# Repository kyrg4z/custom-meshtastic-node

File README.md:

# Custom Meshtastic/Reticulum Node
 
> *Long-range messaging when there's no signal.*

#### Designed by [kyrg4z](https://github.com/kyrg4z)

A custom Meshtastic compatible LoRa communication device that is designed for off-grid messaging in areas where cellular/internet aren't available such as hiking trails, mountains, and forests. This device provides interface for phones to be able to send messages through long range radio through a decentralized mesh network.  

> [!NOTE]
> Read about progress status in JOURNAL.md

### Project Overview
 
A handheld LoRa mesh node built around the Heltec HT-CT62 module (ESP32-C3 + Semtech SX1262), with GPS, a small OLED status display, and a single 18650 cell with USB-C charging and full battery protection. The phone connects over Bluetooth and the node relays messages over 915 MHz LoRa to other nodes in the mesh.

## Story Behind It 

On a chill summer day, while biking in the forest, I tried messaging my friend, but the message didn't go through simply because the cellular signal was too weak there. 
That day I decided to build something of my own, so meeting and sharing location in remote locations would be easier. 
While researching, I learned about LoRa and Meshtastic as well as Ham Radio. I thought Meshtastic would be better for my purposes, so I went with it. Since I wanted to learn PCB design and build something cool, instead of buying a Heltec, Lylygo or SenseCap, I chose to create it myself. I wanted to know how it works and how to mess with it. This project is the result and being hoenst it was quite fun. 
Along the way, I learned how LoRa works(DefCon talks were amazing), how to do PCB design, about ESD protection, and the GNSS system. Probably the hardest part was reading the datasheets and fixing the schematic. 

### The Repository Contains
 
- KiCad schematic and PCB layout
- Gerber, BOM, and centroid files for fabrication and assembly
- Bill of Materials (on-board parts + additional parts)
- Schematic and PCB renders
- Hack Club journal ([JOURNAL.md](JOURNAL.md))

### Hardware
- **MCU + Radio:** Heltec HT-CT62 — ESP32-C3 (RISC-V) + SX1262 LoRa, 902–928 MHz, Wi-Fi/BLE
- **Antennas:** Two onboard IPEX1.0 (U.FL) sockets — LoRa (915 MHz whip via SMA pigtail) and 2.4 GHz (flex antenna for BLE)
- **GNSS:** u-blox SAM-M10Q with built-in patch antenna (UART)
- **Display:** 0.91" 128×32 SSD1306 OLED (I2C)
- **Battery:** 1× 18650 Li-ion in a Keystone 1042 holder
- **Charging:** TI BQ24074 USB charger with power-path management
- **Protection:** DW01A + SI6968BEDQ dual-MOSFET cell protection, 1.5 A resettable PTC fuse
- **Regulation:** TI TPS63001 buck-boost → 3.3 V (stays regulated across the full battery range)
- **USB:** USB-C (USB 2.0) wired directly to the ESP32-C3's native USB, USBLC6-2SC6 ESD protection
- **Battery monitoring:** Voltage divider to an ADC pin
- **Controls/Status:** Reset + Boot buttons, charge-status LED

### PCB Design
 
- 2-layer PCB, 50 × 100 mm
- 0603 passives, 0805 for bulk capacitors
- ENIG surface finish
- Fabricated and assembled by PCBWay (OLED hand-soldered)

No enclosure is part of this submission. The board is meant to be tested bare first, and a case may come in a later revision.

## Firmware
 
- Meshtastic
- Flashed over USB-C
- Planning to implement Reticulum support  
- Status: not yet flashed (waiting on boards)

## 3D Model

Full board assembly with every component: [PRODUCTION/PCB.step](PRODUCTION/PCB.step)

| Top | Bottom |
| :---: | :---: |
|  |  |

> [!NOTE]
> U1 (HT-CT62), U2 (SAM-M10Q) and the OLED carrier board/header (U3) are dimensioned stand-in models generated with CadQuery, since no vendor STEP was available.

## Preview

Interactive KiCad viewer powered by [KiCanvas](https://kicanvas.org):

- **[Open schematic in KiCanvas](https://kicanvas.org/?github=https%3A%2F%2Fgithub.com%2Fkyrg4z%2Fcustom-meshtastic-node%2Fblob%2Fmain%2FPCB%2FPCB.kicad_sch)**
- **[Open PCB layout in KiCanvas](https://kicanvas.org/?github=https%3A%2F%2Fgithub.com%2Fkyrg4z%2Fcustom-meshtastic-node%2Fblob%2Fmain%2FPCB%2FPCB.kicad_pcb)** 

### Schematic 

### PCB snapshot

| Front | Back |
| :---: | :---: |
|  |  |

## Bill Of Materials:

### PCB (assembled by PCBWay):
 
| #  | Reference | Qty | Manufacturer | Manufacturer Part # | Value | Footprint |
| --- | --- | --- | --- | --- | --- | --- |
| 1  | C1 | 1 | Murata Electronics | GRT188R61H105KE13D | 1uF | Capacitor_SMD:C_0603_1608Metric |
| 2  | C2,C3,C5,C6,C7,C10,C12,C15 | 8 | Cal-Chip Electronics, Inc. | GMC21X7R106K25NT | 10uF | Capacitor_SMD:C_0805_2012Metric |
| 3  | C8,C9,C11,C16,C18,C20,C21 | 7 | Murata Electronics | GCJ188R71E104KA12D | 100nF | Capacitor_SMD:C_0603_1608Metric |
| 4  | C13 | 1 | YAGEO | CC0603KRX5R8BB225 | 2.2uF | Capacitor_SMD:C_0603_1608Metric |
| 5  | D1 | 1 | Lite-On Inc. | LTST-C191KRKT | CHG | LED_SMD:LED_0603_1608Metric |
| 6  | F1 | 1 | Littelfuse Inc. | 1206L150SLYR | 1.5A PTC | Fuse:Fuse_1206_3216Metric |
| 7  | J1 | 1 | Korean Hroparts Elec | TYPE-C-31-M-12 | USB-C | Connector_USB:USB_C_Receptacle_HRO_TYPE-C-31-M-12 |
| 8  | J2 | 1 | Keystone Electronics | 1042 | 18650 | Battery:BatteryHolder_Keystone_1042_1x18650 |
| 9  | L1 | 1 | Bourns Inc. | SRN3015-2R2M | 2.2uH | Inductor_SMD:L_Taiyo-Yuden_NR-30xx |
| 10 | Q1 | 1 | Vishay Siliconix | SI6968BEDQ-T1-GE3 | SI6968BEDQ | Package_SO:TSSOP-8_4.4x3mm_P0.65mm |
| 11 | R1,R2 | 2 | Bourns Inc. | CR0603-FX-5101ELF | 5.1k | Resistor_SMD:R_0603_1608Metric |
| 12 | R3,R4 | 2 | YAGEO | RC0603FR-0722RL | 22 | Resistor_SMD:R_0603_1608Metric |
| 13 | R5 | 1 | YAGEO | RC0603FR-07100RL | 100 | Resistor_SMD:R_0603_1608Metric |
| 14 | R6 | 1 | YAGEO | RC0603FR-073KL | 3k | Resistor_SMD:R_0603_1608Metric |
| 15 | R7 | 1 | YAGEO | RC0603FR-073K09L | 3.09k | Resistor_SMD:R_0603_1608Metric |
| 16 | R8,R9 | 2 | YAGEO | RC0603FR-074K7L | 4.7k | Resistor_SMD:R_0603_1608Metric |
| 17 | R10,R11,R19,TH1 | 4 | YAGEO | AR0603FR-0710KL | 10k | Resistor_SMD:R_0603_1608Metric |
| 18 | R14,R15 | 2 | YAGEO | RC0603FR-07100KL | 100k | Resistor_SMD:R_0603_1608Metric |
| 19 | R16 | 1 | YAGEO | RC0603FR-07470RL | 470 | Resistor_SMD:R_0603_1608Metric |
| 20 | R17,R18 | 2 | YAGEO | RC0603FR-071KL | 1k | Resistor_SMD:R_0603_1608Metric |
| 21 | SW1,SW2 | 2 | C&K | PTS810SJS250SMTR LFS | Reset / Boot | Button_Switch_SMD:SW_SPST_PTS810 |
| 22 | U1 | 1 | Heltec Automation | HT-CT62 (902–928 MHz) | HT-CT62 | RF_Module:Heltec_HT-CT62 |
| 23 | U2 | 1 | u-blox | SAM-M10Q-00B | SAM-M10Q | RF_GPS:ublox_SAM-M8Q |
| 24 | U4 | 1 | Texas Instruments | TPS63001DRCR | TPS63001 | Package_SON:Texas_DRC0010J_ThermalVias |
| 25 | U6 | 1 | Texas Instruments | BQ24074RGTR | BQ24074 | Package_DFN_QFN:VQFN-16-1EP_3x3mm_P0.5mm_EP1.6x1.6mm |
| 26 | U7 | 1 | Shenzhen Slkormicro | DW01A | DW01A | Package_TO_SOT_SMD:SOT-23-6 |
| 27 | U8 | 1 | STMicroelectronics | USBLC6-2SC6 | USBLC6-2SC6 | Package_TO_SOT_SMD:SOT-23-6 |

### Additional Parts (per 2 nodes):
 
| Part / Item | Category | Qty | Price (1 item) | Line total | Provider | Link |
| --- | --- | --- | --- | --- | --- | --- |
| **Custom PCB (fab + assembly, 2 assembled of 5)** | PCB | 2 | - | $79.34 USD + parts quote | PCBWay | - |
| **ER-OLEDM0.91-1B-I2C 0.91" OLED** | Display | 3 | $2.80 USD | $8.40 USD | BuyDisplay | [Link](https://www.buydisplay.com/i2c-blue-0-91-inch-oled-display-module-128x32-arduino-raspberry-pi) |
| **Pulse W9015M U.FL → SMA bulkhead pigtail** | LoRa antenna cable | 2 | $7.53 CAD | $15.06 CAD | Digi-Key | [Link](https://www.digikey.ca/en/products/detail/pulse-electronics/W9015M/2267912) |
| **Abracon AEACAC054010-S915 915 MHz whip** | LoRa antenna | 2 | $10.40 CAD | $20.80 CAD | Digi-Key | [Link](https://www.digikey.ca/en/products/detail/abracon-llc/AEACAC054010-S915/9962429) |
| **Ezurio 001-0014 2.4 GHz FlexPIFA (U.FL)** | BLE antenna | 2 | $7.38 CAD | $14.76 CAD | Digi-Key | [Link](https://www.digikey.ca/en/products/detail/ezurio/001-0014/4732758) |
| **18650 Li-ion cell** | Battery | 2 | - | already owned | - | - |
| — | | | | | | |

## Assembly Instructions
 
### PCB:
 
The board is fabricated and assembled by PCBWay. U3 (OLED) is marked DNP and is soldered by hand.

1. Check the GND / VCC / SCL / SDA labels on the OLED against the board silkscreen, then solder its 4-pin header into U3.
2. Plug the U.FL end of the SMA pigtail into the **LoRa** socket on the HT-CT62 and screw on the 915 MHz whip.
3. Plug the 2.4 GHz flex antenna into the **2.4G** socket on the HT-CT62 and stick it to the inside of the case.
4. Insert an 18650 cell, watching polarity.

> [!WARNING]
> Don't power the node with the LoRa antenna disconnected. Transmitting without a load can damage the SX1262.

### First power up 

1. Connect USB-C only 
2. Insert the battery and confirm the charge LED behaves as expected.
3. Connect antennas, then flash firmware over USB-C.

## Licensing
 
Copyright © 2026 kyrg4z
 
| Directory | License |
| --- | --- |
| `PCB/` | [CERN Open Hardware Licence Version 2 - Strongly Reciprocal](https://ohwr.org/cern_ohl_s_v2.txt) — see [`LICENSE-HARDWARE`](LICENSE-HARDWARE) |
| `images/`, `JOURNAL.md` | [Creative Commons Attribution-ShareAlike 4.0 International](https://creativecommons.org/licenses/by-sa/4.0/) — see [`LICENSE-CONTENT`](LICENSE-CONTENT) |

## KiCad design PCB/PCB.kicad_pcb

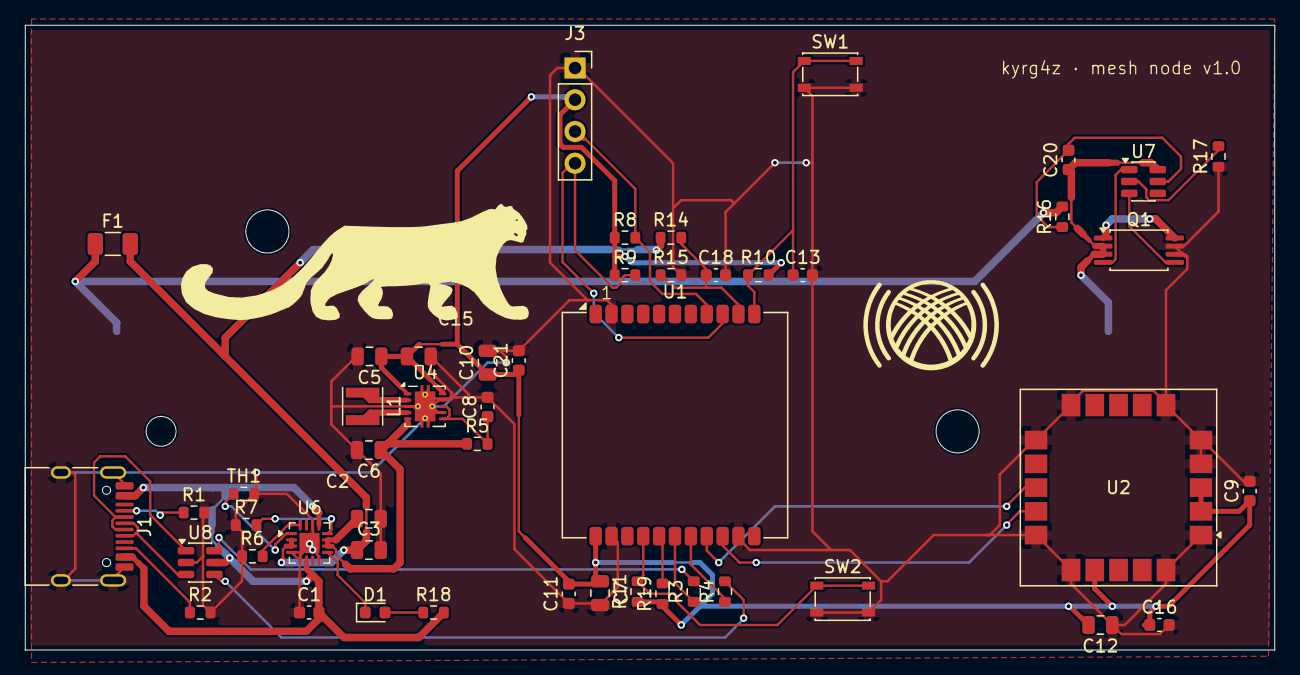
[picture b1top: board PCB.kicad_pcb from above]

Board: 2 copper layers, 100.0 x 50.0 mm, 50 parts (1 on the bottom side), 36 nets.

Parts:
C1: 1uF; C_0603_1608Metric
C2, C3, C5, C6, C7, C10, C12, C15: 10uF; C_0805_2012Metric
C8, C9, C11, C16, C18, C20, C21: 100nF; C_0603_1608Metric
C13: 2.2uF; C_0603_1608Metric
D1: CHG; LED_0603_1608Metric
F1: 1206L150SLYR; Fuse_1206_3216Metric
J1: USB_C_Receptacle_USB2.0_16P; USB_C_Receptacle_HRO_TYPE-C-31-M-12
J2: 18650; BatteryHolder_Keystone_1042_1x18650
J3: OLED_0.91in_I2C; PinSocket_1x04_P2.54mm_Vertical
L1: 2.2uH; L_Taiyo-Yuden_NR-30xx
Q1: SI6968BEDQ; TSSOP-8_4.4x3mm_P0.65mm
R1, R2: 5.1k; R_0603_1608Metric
R3, R4: 22; R_0603_1608Metric
R5: 100; R_0603_1608Metric
R6: 3k; R_0603_1608Metric
R7: 3.09k; R_0603_1608Metric
R8, R9: 4.7k; R_0603_1608Metric
R10, R11, R19: 10k; R_0603_1608Metric
R14, R15: 100k; R_0603_1608Metric
R16: 470; R_0603_1608Metric
R17, R18: 1k; R_0603_1608Metric
SW1: SW_Push_Reset; SW_SPST_PTS810
SW2: SW_Push_Boot; SW_SPST_PTS810
TH1: 10k; R_0603_1608Metric
U1: HT-CT62; Heltec_HT-CT62
U2: SAM-M10Q; ublox_SAM-M8Q
U4: TPS63001; Texas_DRC0010J_ThermalVias
U6: BQ24074RGT; VQFN-16-1EP_3x3mm_P0.5mm_EP1.6x1.6mm
U7: DW01A; SOT-23-6
U8: USBLC6-2SC6; SOT-23-6

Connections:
+3V3: C5.1, C7.1, C9.1, C10.1, C11.2, C12.2, C15.1, C16.1, C21.1, J3.2, R8.1, R9.1, R10.2, R11.1, R19.1, U1.12 (VDD), U2.2 (VCC_IO), U2.3 (V_BCKP), U2.17 (VCC), U4.1 (VOUT), U4.10 (FB)
+BATT: C3.1, F1.2, R14.1, U6.2 (BAT), U6.3 (BAT)
GND: C1.1, C2.2, C3.2, C5.2, C6.2, C7.2, C8.2, C9.2, C10.2, C11.1, C12.1, C13.2, C15.2, C16.2, C18.2, C21.2, J1.A1 (GND), J1.A12 (GND), J1.B1 (GND), J1.B12 (GND), J1.SH (SHIELD), J3.1, Q1.6 (S2), Q1.7 (S2), R1.2, R2.2, R6.1, R7.1, R15.2, R17.1, SW1.2, SW2.2, TH1.2, U1.2 (GND), U1.13 (GND), U1.21 (GND), U2.1 (GND), U2.4 (GND), U2.5 (GND), U2.6 (GND), U2.10 (GND), U2.11 (GND), U2.15 (GND), U2.16 (GND), U2.20 (GND), U4.3 (PGND), U4.7 (PS/SYNC), U4.9 (GND), U4.11 (PGND), U6.4 (~CE), U6.5 (EN2), U6.8 (VSS), U6.14 (TMR), U6.17 (VSS), U8.2 (GND)
GNSS_RX: U1.20 (GPIO21_TXD), U2.14 (RXD)
GNSS_TX: U1.19 (GPIO20_RXD), U2.13 (TXD)
unnamed: D1.2 (A), R18.1
unnamed: D1.1 (K), U6.9 (~CHG)
unnamed: J1.A5 (CC1), R1.1
unnamed: J1.B5 (CC2), R2.1
unnamed: J1.A6 (D+), J1.B6 (D+), U8.3 (I/O2)
unnamed: J1.A7 (D-), J1.B7 (D-), U8.1 (I/O1)
unnamed: F1.1, J2.1, R16.2
unnamed: C20.1, J2.2, Q1.2 (S1), Q1.3 (S1), U7.6 (GND)
unnamed: Q1.1 (D), Q1.8 (D)
unnamed: Q1.4 (G1), U7.1 (OD)
unnamed: Q1.5 (G2), U7.3 (OC)
unnamed: C13.1, R10.1, SW1.1, U1.11 (EN)
unnamed: R19.2, U1.16 (GPIO8)
unnamed: R11.2, SW2.1, U1.15 (GPIO9)
unnamed: R3.1, U1.17 (GPIO18_DN)
unnamed: R4.1, U1.18 (GPIO19_DP)
unnamed: C8.1, R5.2, U4.6 (EN), U4.8 (VINA)
unnamed: L1.2, U4.4 (L1)
unnamed: L1.1, U4.2 (L2)
unnamed: R7.2, U6.12 (ILIM)
unnamed: R6.2, U6.16 (ISET)
unnamed: TH1.1, U6.1 (TS)
unnamed: R17.2, U7.2 (CS)
unnamed: C20.2, R16.1, U7.5 (VCC)
OLED_SCL: J3.3, R8.2, U1.8 (GPIO2)
OLED_SDA: J3.4, R9.2, U1.9 (GPIO1)
SYS: C2.1, C6.1, R5.1, U4.5 (VIN), U6.10 (OUT), U6.11 (OUT)
USB_D+: R4.2, U8.4 (I/O2)
USB_D-: R3.2, U8.6 (I/O1)
VBAT_SENSE: C18.1, R14.2, R15.1, U1.10 (GPIO0)
VBUS_5V: C1.2, J1.A4 (VBUS), J1.A9 (VBUS), J1.B4 (VBUS), J1.B9 (VBUS), R18.2, U6.6 (EN1), U6.13 (IN), U8.5 (VBUS)

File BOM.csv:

#,Reference,Value,Manufacturer,Manufacturer Part #,Footprint,Notes,,,,,
1,C1,1uF,Murata Electronics,GRT188R61H105KE13D,Capacitor_SMD:C_0603_1608Metric,,,,,,
2,"C2,C3,C5,C6,C7,C10,C12,C15",10uF,"Cal-Chip Electronics, Inc.",GMC21X7R106K25NT,Capacitor_SMD:C_0805_2012Metric,,,,,,
3,"C8,C9,C11,C16,C18,C20,C21",100nF,Murata Electronics,GCJ188R71E104KA12D,Capacitor_SMD:C_0603_1608Metric,,,,,,
4,C13,2.2uF,YAGEO,CC0603KRX5R8BB225,Capacitor_SMD:C_0603_1608Metric,,,,,,
5,D1,CHG,Lite-On Inc.,LTST-C191KRKT,LED_SMD:LED_0603_1608Metric,Charge status LED,,,,,
6,F1,1.5A PTC,Littelfuse Inc.,1206L150SLYR,Fuse:Fuse_1206_3216Metric,Resettable fuse,,,,,
7,J1,USB-C 16P,Korean Hroparts Elec,TYPE-C-31-M-12,Connector_USB:USB_C_Receptacle_HRO_TYPE-C-31-M-12,,,,,,
8,J2,18650 holder,Keystone Electronics,1042,Battery:BatteryHolder_Keystone_1042_1x18650,,,,,,
9,L1,2.2uH,Bourns Inc.,SRN3015-2R2M,Inductor_SMD:L_Taiyo-Yuden_NR-30xx,Check pads vs SRN3015 datasheet,,,,,
10,Q1,SI6968BEDQ,Vishay Siliconix,SI6968BEDQ-T1-GE3,Package_SO:TSSOP-8_4.4x3mm_P0.65mm,Pin-compatible with FS8205A,,,,,
11,"R1,R2",5.1k,Bourns Inc.,CR0603-FX-5101ELF,Resistor_SMD:R_0603_1608Metric,USB-C CC pull-downs,,,,,
12,"R3,R4",22,YAGEO,RC0603FR-0722RL,Resistor_SMD:R_0603_1608Metric,USB D+/D- series,,,,,
13,R5,100,YAGEO,RC0603FR-07100RL,Resistor_SMD:R_0603_1608Metric,,,,,,
14,R6,3k,YAGEO,RC0603FR-073KL,Resistor_SMD:R_0603_1608Metric,,,,,,
15,R7,3.09k,YAGEO,RC0603FR-073K09L,Resistor_SMD:R_0603_1608Metric,,,,,,
16,"R8,R9",4.7k,YAGEO,RC0603FR-074K7L,Resistor_SMD:R_0603_1608Metric,I2C pull-ups,,,,,
17,"R10,R11,R19,TH1",10k,YAGEO,AR0603FR-0710KL,Resistor_SMD:R_0603_1608Metric,TH1 = fixed 10k (disables BQ24074 temp sensing),,,,,
18,"R14,R15",100k,YAGEO,RC0603FR-07100KL,Resistor_SMD:R_0603_1608Metric,Battery voltage divider,,,,,
19,R16,470,YAGEO,RC0603FR-07470RL,Resistor_SMD:R_0603_1608Metric,,,,,,
20,"R17,R18",1k,YAGEO,RC0603FR-071KL,Resistor_SMD:R_0603_1608Metric,,,,,,
21,"SW1,SW2",Reset / Boot,C&K,PTS810SJS250SMTR LFS,Button_Switch_SMD:SW_SPST_PTS810,,,,,,
22,U1,HT-CT62,Heltec Automation,HT-CT62 902-928MHz,RF_Module:Heltec_HT-CT62,"heltec.org/project/ht-ct62. Gentle reflow profile, shield can may shift",,,,,
23,U2,SAM-M10Q,u-blox,SAM-M10Q-00B,RF_GPS:ublox_SAM-M8Q,Pin-compatible with SAM-M8Q footprint,,,,,
24,U4,TPS63001,Texas Instruments,TPS63001DRCR,Package_SON:Texas_DRC0010J_ThermalVias,3.3 V buck-boost,,,,,
25,U6,BQ24074,Texas Instruments,BQ24074RGTR,Package_DFN_QFN:VQFN-16-1EP_3x3mm_P0.5mm_EP1.6x1.6mm,Charger / power path,,,,,
26,U7,DW01A,"Shenzhen Slkormicro Semicon Co., Ltd.",DW01A,Package_TO_SOT_SMD:SOT-23-6,Battery protection,,,,,
27,U8,USBLC6-2SC6,STMicroelectronics,USBLC6-2SC6,Package_TO_SOT_SMD:SOT-23-6,USB ESD protection,,,,,
,,,,,,,,,,,
,,,,,,,,,,,
Additional Parts,,,,,,,,,,,
#,Part,Category,Manufacturer,Manufacturer Part #,Supplier,Qty,Unit price,Currency,Line total,Link,Notes
1,"0.91"" 128x32 I2C OLED (blue)",Display,EastRising,ER-OLEDM0.91-1B-I2C,BuyDisplay,3,$2.80,USD,$8.40,https://www.buydisplay.com/i2c-blue-0-91-inch-oled-display-m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,U3 (DNP). 2 + 1 spare. Hand-solder; check pin order vs silkscreen.
2,"U.FL to SMA female bulkhead pigtail, 15""",LoRa antenna cable,Pulse Electronics,W9015M,Digi-Key Canada,2,$7.53,CAD,$15.06,https://www.digikey.ca/en/products/detail/pulse-electronics/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,"SMA (not RP-SMA). Shorter W9006M (6"") is the same price if 15"" is too long."
3,"915 MHz whip antenna, SMA male",LoRa antenna,Abracon LLC,AEACAC054010-S915,Digi-Key Canada,2,$10.40,CAD,$20.80,https://www.digikey.ca/en/products/detail/abracon-llc/AEACAC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,"880-950 MHz, 2 dBi. Screws onto the pigtail."
4,"2.4 GHz FlexPIFA antenna, U.FL",BLE antenna,Ezurio,001-0014,Digi-Key Canada,2,$7.38,CAD,$14.76,https://www.digikey.ca/en/products/detail/ezurio/001-0014/4732758,"Adhesive, 100 mm cable. Plugs into the 2.4G socket on U1."
5,18650 Li-ion cell,Battery,-,-,Already owned,2,-,CAD,-,,Already have these.
